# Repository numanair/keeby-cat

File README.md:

# Keeby Cat

This is the hardware repository for the Keeby Cat macropad. Developement is ongoing.

## Intro

Keeby Cat is a highly configurable macropad with multiple fader and knob layouts. The "standard" build features 3x4 keys with a rotary encoder and an 128x32 pixel OLED display. A full keyswitch build is 3x5 keys with the top row offset vertically by 0.25u. Up to five rotary encoders can be used in specified locations. One to three faders (linear potentiometers) can be used in place of the lower key columns.

## Firmware

Vial is the standard firmware for Keeby Cat as it allows key and encoder reassignment without recompiling firmware.
Firmware source is located here: [github.com/numanair/vial-qmk](https://github.com/numanair/vial-qmk/tree/vial/keyboards/returntoparadise/keeby_cat)  
**Note:** Firmware has not yet been completed for all variations. As such not all variants have been tested yet. However, the groundwork is there and it should not be too complicated to create these firmware variations.

## Layouts and Configurations

The default configuration is 3x4 keys with a single knob and an OLED screen.

The maximum keyswitch layout is 3x5.

### Rotary Encoder Knobs

Nine special key locations can accept encoder knobs, however only five knobs can be wired up at once.

Potential knob locations are:  
The left and right columns of the lower 4 keys, but with only one from each *row* being installed.
The top left corner.

### OLED Screen

An optional display can show layer information, key-states, and graphics. It replaces the top right pair of keyswitches.

## Cases

Two types of cases are available. The low-profile option is more minimal in material usage and features a 3-degree tilt. The high-profile case (`keeby_cat_case_retro-hi_v1.0.FCStd`) has a 5-degree tilt, but is actually slightly lower profile at the front. USB port placement on the high-profile case is currently more refined. It is designed for a Blue Pill board with a mid-mount micro USB port. These refinements will eventually be integrated into the low-profile case as well. To modify these CAD files, please use [realthunder's FreeCAD fork, stable build 2022.07.09.](https://github.com/realthunder/FreeCAD/releases/tag/2022.07.09-edge)

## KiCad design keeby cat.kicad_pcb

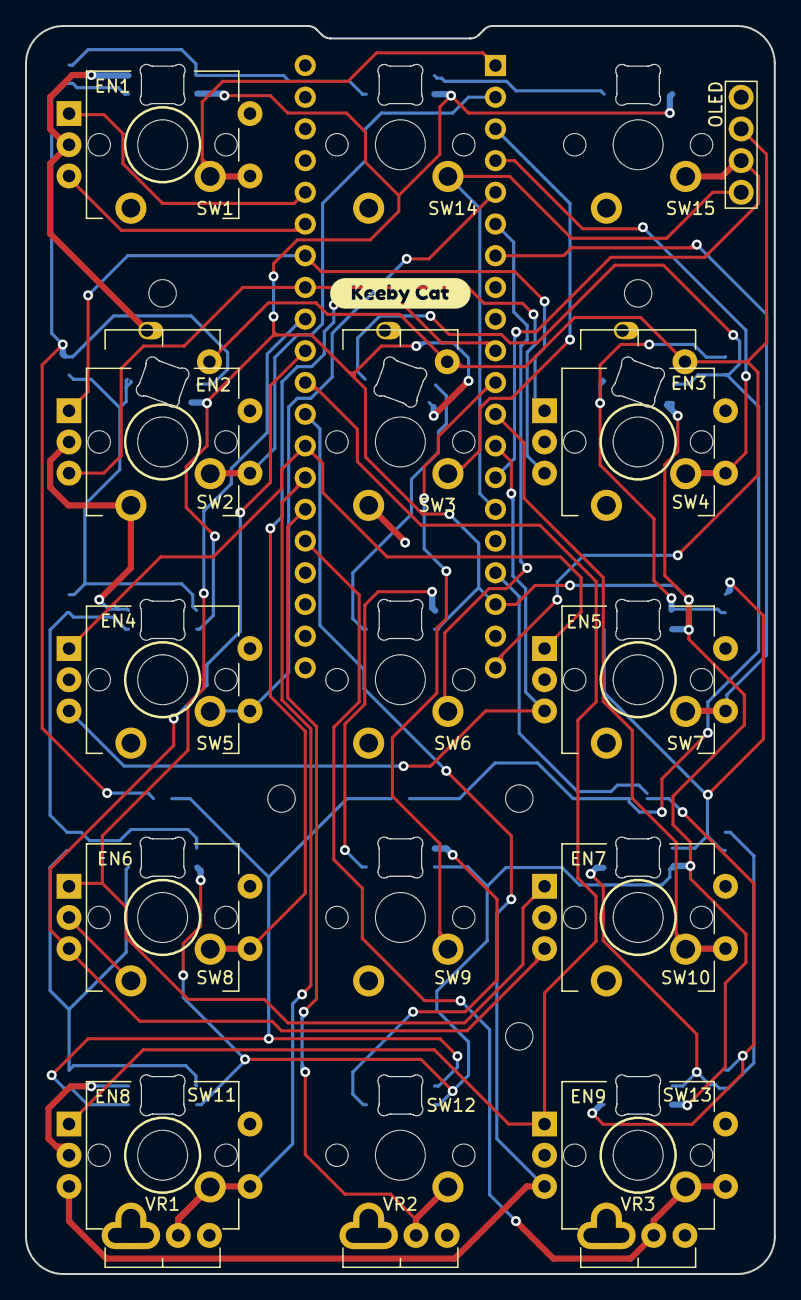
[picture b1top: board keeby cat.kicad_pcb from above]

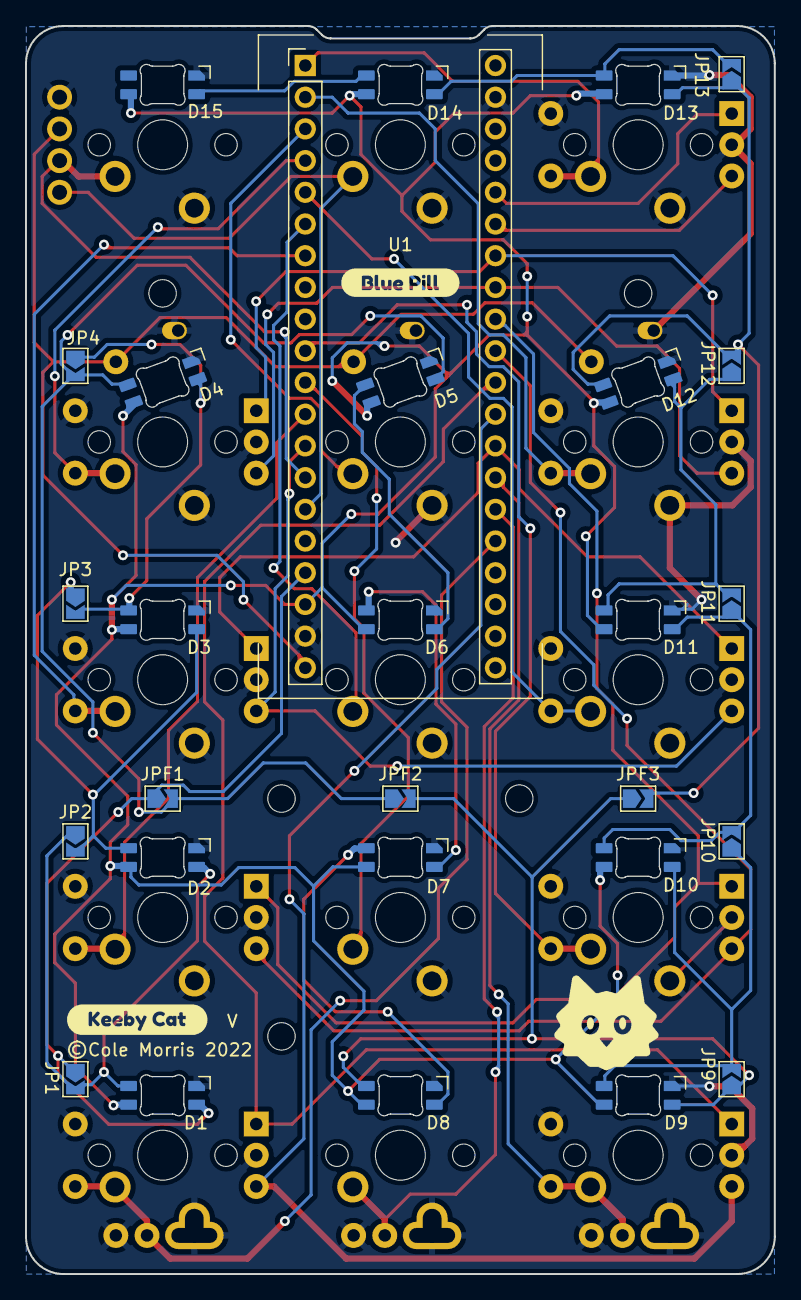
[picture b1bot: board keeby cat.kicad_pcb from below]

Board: 2 copper layers, 60.0 x 100.0 mm, 64 parts (15 on the bottom side), 43 nets.

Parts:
D1, D2, D3, D6, D7, D8, D9, D10, D11, D13, D14, D15: SK6812MINI-E; LED_MX_SK6812MINI-E
D4, D5, D12: SK6812MINI-E; LED_MX_SK6812MINI-E_rotated
EN1, EN2, EN3, EN4, EN5, EN6, EN7, EN8, EN9: RotaryEncoder_Switch; RotaryEncoder_Alps_EC11E-Switch_Vertical_H20mm_nomount_alt
H1, H2, H3, H4, H5: MountingHole; MountingHole_2.2mm_M2_DIN965
JP1, JP2, JP3, JP4, JP9, JP10, JP11, JP12, JP13: SolderJumper_2_Open; SolderJumper-2_P1.3mm_Open_TrianglePad1.0x1.5mm
JPF1, JPF2, JPF3: SolderJumper_2_Open; SolderJumper-2_P1.3mm_Open_TrianglePad1.0x1.5mm
OL1: OLED; OLED_v2
SW1, SW2, SW3, SW4, SW5, SW6, SW7, SW8, SW9, SW10, SW14, SW15: SW_Push; CherryMX_1u_north
SW11, SW12, SW13: SW_Push; CherryMX_1u_north_potcombo
U1: BluePill_V1.1; BluePill_bttn_basic
VR1, VR2, VR3: L_POT_Dual_PS60M_combo; PS60M Single-pin
kibuzzard-6226FF10, kibuzzard-6226FF10#2: G***; kibuzzard-6226FF10
kibuzzard-6227022E: G***; kibuzzard-6227022E

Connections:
+3V3: OL1.3 (VCC), U1.20 (3V3), VR1.3B, VR2.3B, VR3.3B
+5V: D1.1 (VDD), D2.1 (VDD), D3.1 (VDD), D4.1 (VDD), D5.1 (VDD), D6.1 (VDD), D7.1 (VDD), D8.1 (VDD), D9.1 (VDD), D10.1 (VDD), D11.1 (VDD), D12.1 (VDD), D13.1 (VDD), D14.1 (VDD), D15.1 (VDD), U1.18 (5V)
ENC1A: EN1.A, U1.36 (PB11)
ENC1B: EN1.B, U1.35 (PB10)
ENC2A: EN2.A, EN3.A, U1.34 (PB1)
ENC2B: EN2.B, EN3.B, U1.33 (PB0)
ENC3A: EN4.A, EN5.A, U1.28 (PA3)
ENC3B: EN4.B, EN5.B, U1.13 (PB5)
ENC4A: EN6.A, EN7.A, U1.32 (PA7)
ENC4B: EN6.B, EN7.B, U1.31 (PA6)
ENC5A: EN8.A, EN9.A, U1.30 (PA5)
ENC5B: EN8.B, EN9.B, U1.29 (PA4)
GND: D1.3 (GND), D2.3 (GND), D3.3 (GND), D4.3 (GND), D5.3 (GND), D6.3 (GND), D7.3 (GND), D8.3 (GND), D9.3 (GND), D10.3 (GND), D11.3 (GND), D12.3 (GND), D13.3 (GND), D14.3 (GND), D15.3 (GND), EN1.C, EN1.S2, EN2.C, EN2.S2, EN3.C, EN3.S2, EN4.C, EN4.S2, EN5.C, EN5.S2, EN6.C, EN6.S2, EN7.C, EN7.S2, EN8.C, EN8.S2, EN9.C, EN9.S2, OL1.4 (GND), SW1.2, SW2.2, SW3.2, SW4.2, SW5.2, SW6.2, SW7.2, SW8.2, SW9.2, SW10.2, SW11.2, SW12.2, SW13.2, SW14.2, SW15.2, U1.19 (GND), U1.39 (GND), VR1.1B, VR1.3, VR2.1B, VR2.3, VR3.1B, VR3.3
KEY1: EN1.S1, SW1.1, U1.1 (PB12)
KEY2: EN2.S1, SW2.1, U1.2 (PB13)
KEY3: SW3.1, U1.3 (PB14)
KEY4: EN3.S1, SW4.1, U1.4 (PB15)
KEY5: EN4.S1, SW5.1, U1.5 (PA8)
KEY6: SW6.1, U1.6 (PA9)
KEY7: EN5.S1, SW7.1, U1.7 (PA10)
KEY8: EN6.S1, SW8.1, U1.10 (PA15)
KEY9: SW9.1, U1.11 (PB3)
KEY10: EN7.S1, SW10.1, U1.12 (PB4)
KEY11-POT1: EN8.S1, SW11.1, U1.27 (PA2), VR1.2B
KEY12-POT2: SW12.1, U1.26 (PA1), VR2.2B
KEY13-POT3: EN9.S1, SW13.1, U1.25 (PA0), VR3.2B
LED_DATA: D1.4 (DIN), JP1.1 (A), JPF1.1 (A), U1.17 (PB9)
unnamed: D1.2 (DOUT), D2.4 (DIN), JP1.2 (B), JP2.1 (A)
unnamed: D2.2 (DOUT), D3.4 (DIN), JP2.2 (B), JP3.1 (A)
unnamed: D3.2 (DOUT), D4.4 (DIN), JP3.2 (B), JP4.1 (A)
unnamed: D4.2 (DOUT), D5.4 (DIN), JP4.2 (B), JPF1.2 (B), JPF2.1 (A)
unnamed: D5.2 (DOUT), D6.4 (DIN)
unnamed: D6.2 (DOUT), D7.4 (DIN)
unnamed: D7.2 (DOUT), D8.4 (DIN)
unnamed: D8.2 (DOUT), D9.4 (DIN), JP9.1 (A), JPF2.2 (B), JPF3.1 (A)
unnamed: D10.2 (DOUT), D11.4 (DIN), JP10.2 (B), JP11.1 (A)
unnamed: D9.2 (DOUT), D10.4 (DIN), JP9.2 (B), JP10.1 (A)
unnamed: D11.2 (DOUT), D12.4 (DIN), JP11.2 (B), JP12.1 (A)
unnamed: D12.2 (DOUT), D13.4 (DIN), JP12.2 (B), JP13.1 (A), JPF3.2 (B)
unnamed: D13.2 (DOUT), D14.4 (DIN), JP13.2 (B)
unnamed: D14.2 (DOUT), D15.4 (DIN)
SCL-SW: OL1.2 (SCL), SW15.1, U1.14 (PB6)
SDA-SW: OL1.1 (SDA), SW14.1, U1.15 (PB7)

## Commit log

2022-02-16 add personal library derived parts
2022-02-16 added my modification of marbastlib kicad library
2022-02-16 created Footprints library folder
2022-02-16 Add library files and update paths
2022-02-17 updated libs, positioned jumpers
2022-02-17 oled adjustment
2022-02-17 modified silk outline of front pads
2022-02-17 initial board routing
2022-02-18 routing improvements
2022-02-18 F.silk and via refinement
2022-02-18 update silks and add copper
2022-02-18 cleanup tracks
2022-02-18 shrank board outline to 100mm max
2022-02-18 adjusted routing around holes
2022-02-18 rounded edge cuts for new 100mm size
2022-02-18 move MCU downwards to better fit within new 100mm size
2022-02-19 Fixed pin-sharing faders/keys
2022-02-19 removed extra via
2022-02-19 first implementation of matrix
2022-02-19 add fader to faceplate
2022-02-20 split plate module out
2022-02-20 Now public. Don't try building it yet :)
2022-02-20 more copper
2022-02-20 added bezel to plate
2022-02-20 plate generator now overrides encoders in middle column
2022-02-21 plate cleanup
2022-02-21 more minor plate cleanup
2022-02-25 Centered faders and rotated LEDs
    Experimental solution to make faders centered to lower 4 rows of keys/grid. Requires bending or trimming off an unused pin from the faders.
2022-02-27 Pin relief
2022-02-27 routing and silkscreen improvements
2022-02-27 Added fastener holes to plate
2022-02-27 add option for polyholes countersink
2022-03-08 routing and footprint fixes
2022-03-08 changed text layer for some footprints
2022-03-08 improved thin spots in ground plane, removed via
    also very small routing improvements
2022-03-09 Corrected LED pinout again
2022-03-09 masked top pads for encoders
2022-03-09 LED pins fixed, lots of rerouting
    Corrected LED and routed accordingly. Lots of other misc, changes to improve routing.
2022-03-09 spreadsheet for LED matrix in QMK
2022-03-09 Plate: chamfered edges, other improvements
2022-03-10 minor routing tweaks
2022-03-10 adjusted silkscreen
2022-03-10 refilled zones
2022-03-10 renamed PCB project files
2022-03-17 added cat mascot and silkscreen
2022-03-17 refilled ground plane zone
2022-03-17 refill for plotting v1.0
2022-03-17 plotted gerbers for v1.0
2022-03-18 minor fix for board outline
2022-03-18 add missing STEP file for blue pill
2022-03-28 removed dupe paths and scaled 200%
2022-03-28 adjust schematic graphics
2022-03-29 preview of back of board using PcbDraw
2022-03-29 move mascot graphic
2022-04-13 Plate: Simplified some centering and adjusted holes
2022-05-05 LED matrix file changes for alternate builds
2022-05-05 Base low-profile case
2022-06-29 knob prototyping
2022-07-17 clarify build steps details
2022-07-17 Increase clearance on the top plate
    Clearance for keyswitches has been increased to help compensate for too much 1st layer squish
2022-07-17 Add OLED step and fix paths
2022-07-17 remove redundant STEP model
2022-07-18 removed large STEP from pcb
2022-07-23 Add retro-hi case assembly
    High-profile case designed with FreeCAD linkstage3 daily 20220709
2022-07-23 moved PCB grid origin for better CAD import
2022-07-23 removed large STEP file
2022-07-23 Add FreeCAD details to readme
2022-07-29 removed extra knob CAD file
2022-07-29 Add FreeCAD backups to gitignore
2022-07-29 Update case CAD
    Refined some geometry
    Added small chamfers and fillets to sharp edges on bottom of case
    Recreated constraints and locked other parts
2022-07-29 Apply Spreadsheet value to model
    Make screw holes based on spreadsheet value
2022-08-11 Move kicad schematic
2022-08-17 add missing logic to plate.scad
    add missing logic for keyswitches in the top row
2022-08-17 Move libraries to KiCAD schematic folder
    And update Blue Pill 3D CAD model in board
2022-08-18 add more clearance for screw head to plate
2022-08-18 Add blender backups to gitignore
2022-08-20 Potentiometer covers
    Initial design
2022-08-24 Update keeby_cat_case_TRIO_arc-up.FCStd
    simplify features

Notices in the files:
keeby cat.kicad_pcb:
©Cole Morris 2022
